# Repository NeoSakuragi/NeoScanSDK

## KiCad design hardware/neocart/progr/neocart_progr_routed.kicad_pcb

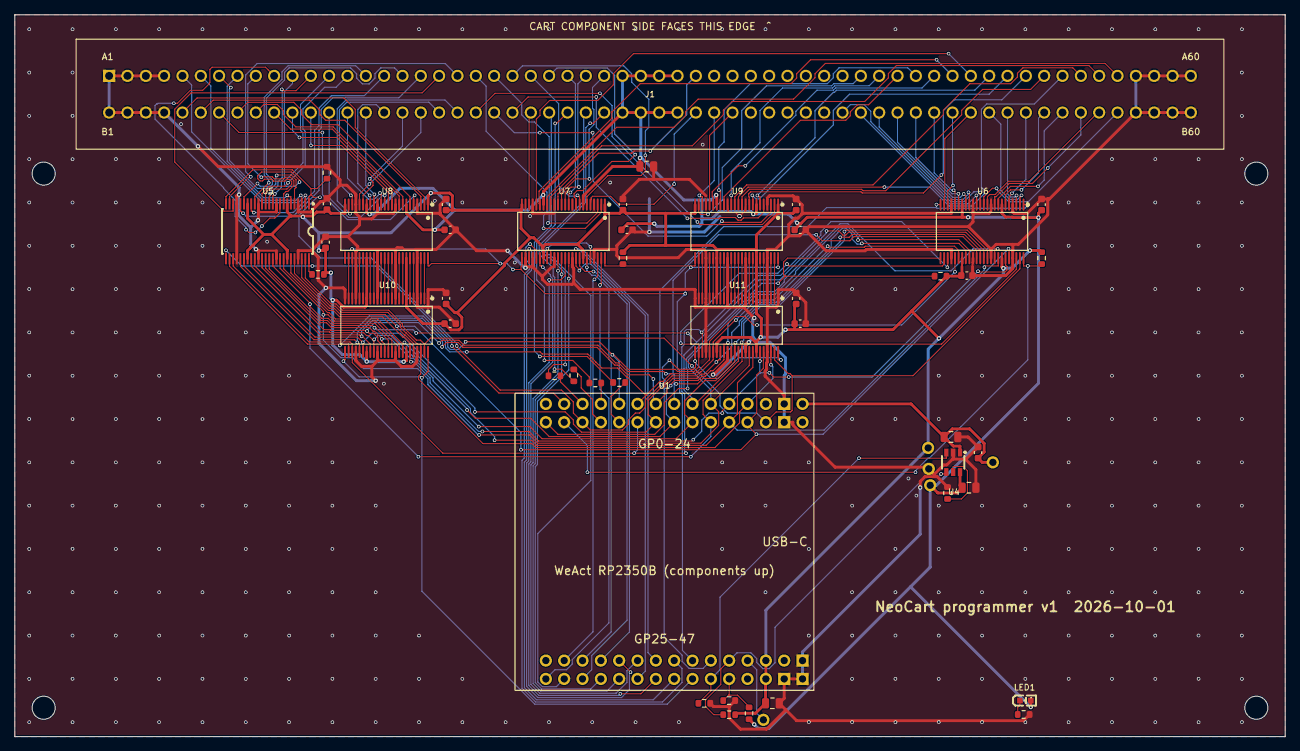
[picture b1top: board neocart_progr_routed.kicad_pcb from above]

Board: 2 copper layers, 176.0 x 100.0 mm, 54 parts (0 on the bottom side), 167 nets.

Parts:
C1, C3, C4, C5: 10u; C_0805_2012Metric
C2, C6, C7, C8, C9, C10, C11, C12, C13, C14, C15, C16, C17, C18, C19: 100n; C_0603_1608Metric
J1: MVS slot; MVS_SLOT_EDAC_345-120
LED1: CART; LED-SMD_L1.6-W0.8-R-RD
MH1, MH2, MH3, MH4: M3; MH_M3
R1, R2, R3, R4, R5, R6, R7, R9, R10: 10k; R_0603_1608Metric
R8: 33k; R_0603_1608Metric
R11, R12, R13, R14, R15: 1k; R_0603_1608Metric
TP1: GND; TP_PTH_1.0
TP2: P3V3; TP_PTH_1.0
TP3: VCART; TP_PTH_1.0
TP4: VBUS; TP_PTH_1.0
TP5: GPIO47; TP_PTH_1.0
U1: WeAct RP2350B; WEACT_RP2350B_CORE
U4: TPS2553; SOT-23-6_L2.9-W1.6-P0.95-LS2.8-BR
U5: 74LVC16245A; TSSOP-48_L12.5-W6.1-P0.50-LS8.1-BL
U6, U7, U8, U9: SN74LVC16T245; TSSOP-48_L12.6-W6.2-P0.50-LS8.1-BL
U10, U11: 74LVC16374A; TSSOP-48_L12.6-W6.2-P0.50-LS8.1-BL

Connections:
A1: J1.B5, U8.2
A2: J1.B6, U8.3
A3: J1.B7, U8.5
A4: J1.B8, U8.6
A5: J1.B9, U8.8
A6: J1.B10, U8.9
A7: J1.B11, U8.11
A8: J1.B12, U8.12
A9: J1.B13, U8.13
A10: J1.B14, U8.14
A11: J1.B15, U8.16
A12: J1.B16, U8.17
A13: J1.B17, U8.19
A14: J1.B18, U8.20
A15: J1.B19, U8.22
A16: J1.B20, U8.23
A17: J1.B21, U9.2
A18: J1.B22, U9.3
A19: J1.B23, U9.5
CLK4M: J1.B34, U9.22
CLK68K: J1.B24, U7.22
D0: J1.A5, U5.2
D1: J1.A6, U5.3
D2: J1.A7, U5.5
D3: J1.A8, U5.6
D4: J1.A9, U5.8
D5: J1.A10, U5.9
D6: J1.A11, U5.11
D7: J1.A12, U5.12
D8: J1.A13, U5.13
D9: J1.A14, U5.14
D10: J1.A15, U5.16
D11: J1.A16, U5.17
D12: J1.A17, U5.19
D13: J1.A18, U5.20
D14: J1.A19, U5.22
D15: J1.A20, U5.23
GND: C1.2, C2.2, C3.2, C4.2, C5.2, C6.2, C7.2, C8.2, C9.2, C10.2, C11.2, C12.2, C13.2, C14.2, C15.2, C16.2, C17.2, C18.2, C19.2, J1.A1, J1.A2, J1.A3, J1.A4, J1.A57, J1.A58, J1.A59, J1.A60, J1.B1, J1.B2, J1.B3, J1.B4, J1.B57, J1.B58, J1.B59, J1.B60, R5.2, R6.2, R8.2, R10.2, R15.2, TP1.1, U1.BI2, U1.BO2, U1.TI1, U1.TO1, U1.TO2, U4.2, U5.4, U5.10, U5.15, U5.21, U5.28, U5.34, U5.39, U5.45, U6.4, U6.10, U6.15, U6.21, U6.28, U6.34, U6.39, U6.45, U7.4, U7.10, U7.15, U7.21, U7.26, U7.28, U7.34, U7.39, U7.45, U8.4, U8.10, U8.15, U8.21, U8.28, U8.34, U8.39, U8.45, U9.4, U9.10, U9.15, U9.21, U9.28, U9.34, U9.39, U9.45, U10.1, U10.4, U10.10, U10.15, U10.21, U10.24, U10.28, U10.34, U10.39, U10.45, U11.1, U11.4, U11.10, U11.15, U11.21, U11.24, U11.28, U11.34, U11.39, U11.45
GPIO47: TP5.1, U1.TI4
G_CLK68K: U1.TO8, U7.27
G_RW: U1.TO15, U7.47
G_SDPMPX: U1.TO9, U7.30
G_SDRMPX: U1.TO10, U7.33
G_nAS: U1.TI14, U7.46
G_nPORTADRS: U1.TI10, U7.35
G_nPORTOEL: U1.TO12, U7.38
G_nPORTOEU: U1.TI12, U7.40
G_nPORTWEL: U1.TO11, U7.36
G_nPORTWEU: U1.TI11, U7.37
G_nROMOE: U1.TO14, U7.44
G_nROMOEL: U1.TO13, U7.41
G_nROMOEU: U1.TI13, U7.43
G_nSDPOE: U1.TI8, U7.29
G_nSDROE: U1.TI9, U7.32
ILIM: R8.1, U4.5
LCLK1: U1.TO7, U10.25, U10.48
LCLK2: U1.TI6, U11.25, U11.48
LED1_K: LED1.2, R15.1
L_A1: U8.47, U10.2
L_A2: U8.46, U10.3
L_A3: U8.44, U10.5
L_A4: U8.43, U10.6
L_A5: U8.41, U10.8
L_A6: U8.40, U10.9
L_A7: U8.38, U10.11
L_A8: U8.37, U10.12
L_A9: U8.36, U10.13
L_A10: U8.35, U10.14
L_A11: U8.33, U10.16
L_A12: U8.32, U10.17
L_A13: U8.30, U10.19
L_A14: U8.29, U10.20
L_A15: U8.27, U10.22
L_A16: U8.26, U10.23
L_A17: U9.47, U11.2
L_A18: U9.46, U11.3
L_A19: U9.44, U11.5
L_CLK4M: U9.27, U11.22
L_SDPA8: U9.35, U11.14
L_SDPA9: U9.33, U11.16
L_SDPA10: U9.32, U11.17
L_SDPA11: U9.30, U11.19
L_SDRA8: U9.43, U11.6
L_SDRA9: U9.41, U11.8
L_SDRA20: U9.40, U11.9
L_SDRA21: U9.38, U11.11
L_SDRA22: U9.37, U11.12
L_SDRA23: U9.36, U11.13
L_nRESET: U9.29, U11.20
L_nSLOTCS: U9.26, U11.23
MD0: U1.BI3, U5.47, U6.47, U10.47, U11.47
MD1: U1.BO4, U5.46, U6.46, U10.46, U11.46
MD2: U1.BI4, U5.44, U6.44, U10.44, U11.44
MD3: U1.BO5, U5.43, U6.43, U10.43, U11.43
MD4: U1.BI5, U5.41, U6.41, U10.41, U11.41
MD5: U1.BO6, U5.40, U6.40, U10.40, U11.40
MD6: U1.BI6, U5.38, U6.38, U10.38, U11.38
MD7: U1.BO7, U5.37, U6.37, U10.37, U11.37
MD8: U1.BI7, U5.36, U6.36, U10.36, U11.36
MD9: U1.BO8, U5.35, U6.35, U10.35, U11.35
MD10: U1.BI8, U5.33, U6.33, U10.33, U11.33
MD11: U1.BO9, U5.32, U6.32, U10.32, U11.32
MD12: U1.BI9, U5.30, U6.30, U10.30, U11.30
MD13: U1.BO10, U5.29, U6.29, U10.29, U11.29
MD14: U1.BI10, U5.27, U6.27, U10.27, U11.27
MD15: U1.BO11, U5.26, U6.26, U10.26, U11.26
P3V3: C5.1, C6.1, C7.1, C8.1, C9.1, C10.1, C11.1, C12.1, C14.1, C16.1, C18.1, R1.2, R2.2, R3.2, R4.2, R7.2, TP2.1, U1.TI3, U1.TO3, U5.7, U5.18, U5.31, U5.42, U6.31, U6.42, U7.1, U7.24, U7.31, U7.42, U8.1, U8.24, U8.31, U8.42, U9.1, U9.24, U9.31, U9.42, U10.7, U10.18, U10.31, U10.42, U11.7, U11.18, U11.31, U11.42
RW: J1.A21, U7.2
SDPA8: J1.A43, U9.14
SDPA9: J1.A44, U9.16
SDPA10: J1.A45, U9.17
SDPA11: J1.A46, U9.19
SDPAD0: J1.B41, U6.13
SDPAD1: J1.B42, U6.14
SDPAD2: J1.B43, U6.16
SDPAD3: J1.B44, U6.17
SDPAD4: J1.B45, U6.19
SDPAD5: J1.B46, U6.20
SDPAD6: J1.B47, U6.22
SDPAD7: J1.B48, U6.23
SDPMPX: J1.A47, U7.19
SDRA8: J1.A49, U9.6
SDRA9: J1.A50, U9.8
SDRA20: J1.A51, U9.9
SDRA21: J1.A52, U9.11
SDRA22: J1.A53, U9.12
SDRA23: J1.A54, U9.13
SDRAD0: J1.B49, U6.2
SDRAD1: J1.B50, U6.3
SDRAD2: J1.B51, U6.5
SDRAD3: J1.B52, U6.6
SDRAD4: J1.B53, U6.8
SDRAD5: J1.B54, U6.9
SDRAD6: J1.B55, U6.11
SDRAD7: J1.B56, U6.12
SDRMPX: J1.A55, U7.16
S_nPDTACK: R14.2, U1.BO13
S_nPWAIT0: R12.2, U1.BO12
S_nPWAIT1: R13.2, U1.BI12
S_nROMWAIT: R11.2, U1.BI11
VBUS: C1.1, C2.1, TP4.1, U1.BO1, U4.1
VCART: C3.1, C4.1, C13.1, C15.1, C17.1, C19.1, J1.A29, J1.A30, J1.A31, J1.A32, J1.B29, J1.B30, J1.B31, J1.B32, LED1.1, R9.1, TP3.1, U4.6, U6.7, U6.18, U7.7, U7.18, U8.7, U8.18, U9.7, U9.18
VCART_EN: R6.1, U1.TO6, U4.3
VCART_SENSE: R9.2, R10.1, U1.TO5
XDIR: R5.1, U1.BI13, U5.1, U5.24, U6.1, U6.24
nAS: J1.A22, U7.3
nOE_D: R1.1, U1.BO14, U5.25, U5.48
nOE_OUT: R4.1, U1.TI7, U7.25, U7.48, U8.25, U8.48, U9.25, U9.48
nOE_VA: R2.1, U1.BI14, U6.48
nOE_VB: R3.1, U1.BI15, U6.25
nPDTACK: J1.B28, R14.1
nPORTADRS: J1.A33, U7.14
nPORTOEL: J1.A26, U7.11
nPORTOEU: J1.A25, U7.9
nPORTWEL: J1.A28, U7.13
nPORTWEU: J1.A27, U7.12
nPWAIT0: J1.B26, R12.1
nPWAIT1: J1.B27, R13.1
nRESET: J1.B35, U9.20
nROMOE: J1.B33, U7.5
nROMOEL: J1.A24, U7.8
nROMOEU: J1.A23, U7.6
nROMWAIT: J1.B25, R11.1
nSDPOE: J1.A48, U7.20
nSDROE: J1.A56, U7.17
nSLOTCS: J1.A42, U9.23
nVCART_FAULT: R7.1, U1.TI5, U4.4

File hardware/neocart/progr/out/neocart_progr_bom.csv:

Comment,Designator,Footprint,LCSC Part #
100n,"C12,C6,C11,C9,C18,C8,C2,C7,C19,C15,C10,C17,C16,C14,C13",C0603,C14663
10k,"R1,R2,R4,R9,R5,R6,R7,R10,R3",R0603,C25804
1k,"R15,R12,R14,R11,R13",R0603,C21190
CART,LED1,LED-SMD_L1.6-W0.8-R-RD,C2286
SN74LVC16T245,"U9,U6,U7,U8",TSSOP-48_L12.6-W6.2-P0.50-LS8.1-BL,C148170
TPS2553,U4,SOT-23-6_L2.9-W1.6-P0.95-LS2.8-BR,C55266
10u,"C3,C5,C4,C1",C0805,C15850
74LVC16245A,U5,TSSOP-48_L12.5-W6.1-P0.50-LS8.1-BL,C548160
74LVC16374A,"U10,U11",TSSOP-48_L12.6-W6.2-P0.50-LS8.1-BL,C6074
33k,R8,R0603,C4216
